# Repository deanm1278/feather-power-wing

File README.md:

# feather-power-wing
a wing to turn on and off a feather board with a signal voltage

This is useful for battery powered applications where you don't wanna waste your mAh on sleep mode or voltage regulators or what have you.

The battery is connected to the VIN and GND pins, and if a voltage applied to the VON pin for a period of time set by R7 (up to 1.5 sec with given values of C1 and R7) then the feather will turn on.

If pin 12 on the feather goes high, the feather will turn itself off. The onboard regulator works with supply voltages up to 15V.

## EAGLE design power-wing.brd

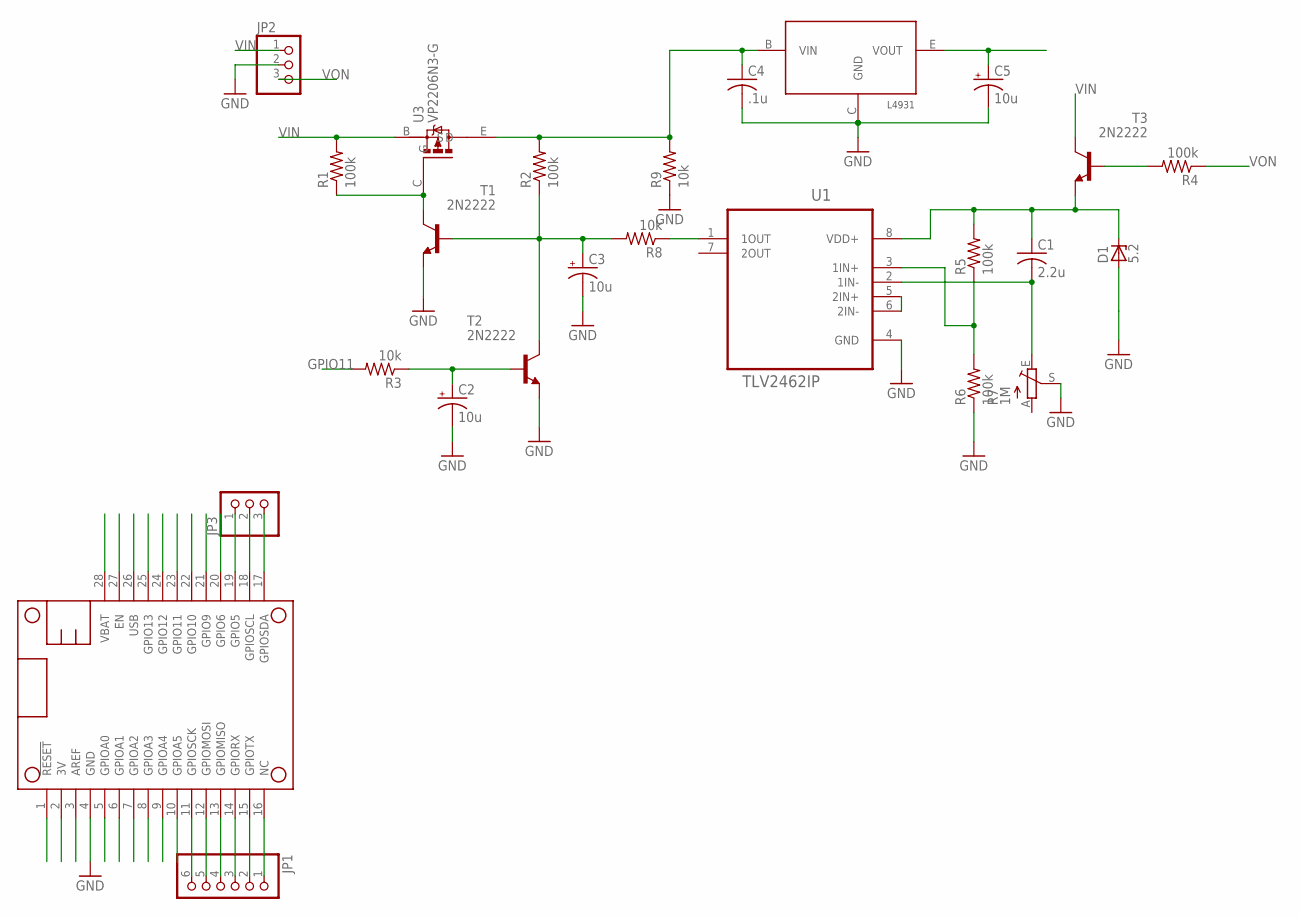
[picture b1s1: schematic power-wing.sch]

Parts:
C1: 2.2u; C025-024X044
C2, C3, C5: 10u; E1,8-4
C4: .1u; C025-024X044
D1: 5.2; DO34Z7
JP1: PINHD-1X6; 1X06
JP2, JP3: PINHD-1X3; 1X03
MS1: FEATHERWING
R1, R2, R4, R5, R6: 100k; 0204/5
R3, R8, R9: 10k; 0204/5
R7: 1M; PT-SPIN
T1, T2, T3: 2N2222; TO92-EBC-OVAL
U1: TLV2462IP; DIP254P762X508-8
U2: L4931; TO92-BCE
U3: VP2206N3-G; TO92-BCE

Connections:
3V: C5.+, MS1.2 (3V), U2.E (VOUT)
AREF: MS1.3 (AREF)
GND: C2.-, C3.-, C4.2, C5.-, JP2.2, MS1.4 (GND), R6.1, R7.S, R9.1, T1.E, T2.E, U1.4 (GND), U2.C (GND)
GPIO11: MS1.23 (GPIO11), R3.2
GPIO12: MS1.24 (GPIO12)
unnamed: JP1.1, MS1.16 (NC)
unnamed: JP1.2, MS1.15 (GPIOTX)
unnamed: JP1.3, MS1.14 (GPIORX)
unnamed: JP1.4, MS1.13 (GPIOMISO)
unnamed: JP1.5, MS1.12 (GPIOMOSI)
unnamed: JP1.6, MS1.11 (GPIOSCK)
unnamed: R1.1, T1.C, U3.C (G)
unnamed: C3.+, R2.1, R8.2, T1.B, T2.C
unnamed: JP3.1, MS1.19 (GPIO5)
unnamed: JP3.2, MS1.18 (GPIOSCL)
unnamed: JP3.3, MS1.17 (GPIOSDA)
unnamed: C2.+, R3.1, T2.B
unnamed: R5.1, R6.2, U1.3 (1IN+)
unnamed: C1.1, D1.C, R5.2, T3.E, U1.8 (VDD+)
unnamed: C1.2, R7.E, U1.2 (1IN-)
unnamed: R4.2, T3.B
unnamed: U1.5 (2IN+), U1.6 (2IN-)
unnamed: R8.1, U1.1 (1OUT)
USB: MS1.26 (USB)
VBAT: MS1.28 (VBAT)
VIN: JP2.1, R1.2, T3.C, U3.B (S)
VON: JP2.3, R4.1
VOUT: C4.1, R2.2, R9.2, U2.B (VIN), U3.E (D)

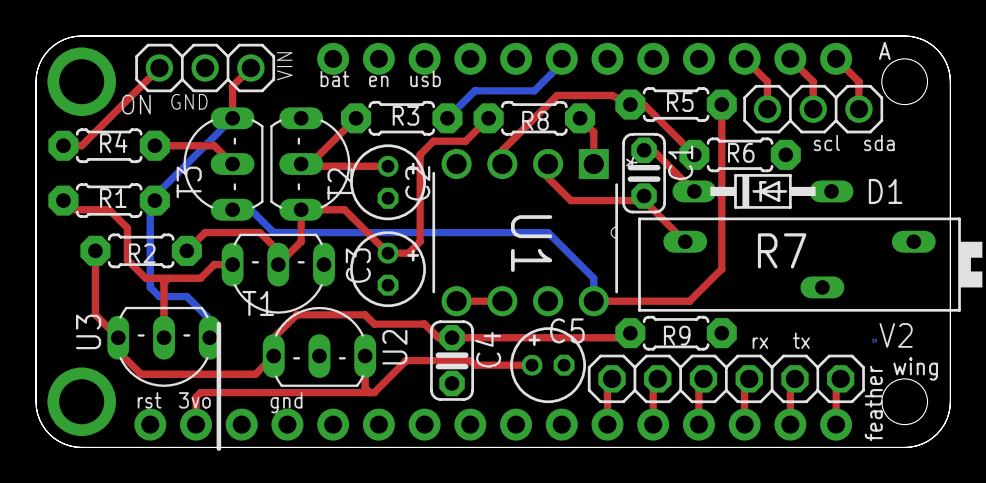
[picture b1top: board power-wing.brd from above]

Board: 2 copper layers, 50.8 x 22.9 mm, 25 parts (0 on the bottom side), 24 nets.

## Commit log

2016-08-17 DM: added board image
2016-09-06 off switch to GPIO11 instead of 12 since that is used for sleep
2016-09-07 lets use some smaller parts
2016-09-09 fixed the names
